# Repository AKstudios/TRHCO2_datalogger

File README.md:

# T/RH/CO2 data logger
A temperature, relative humidity and carbon dioxide data logger that stores time-stamped data in a microSD card at specific logging intervals.

<p align="center">
  
  <br></br>
  
</p>

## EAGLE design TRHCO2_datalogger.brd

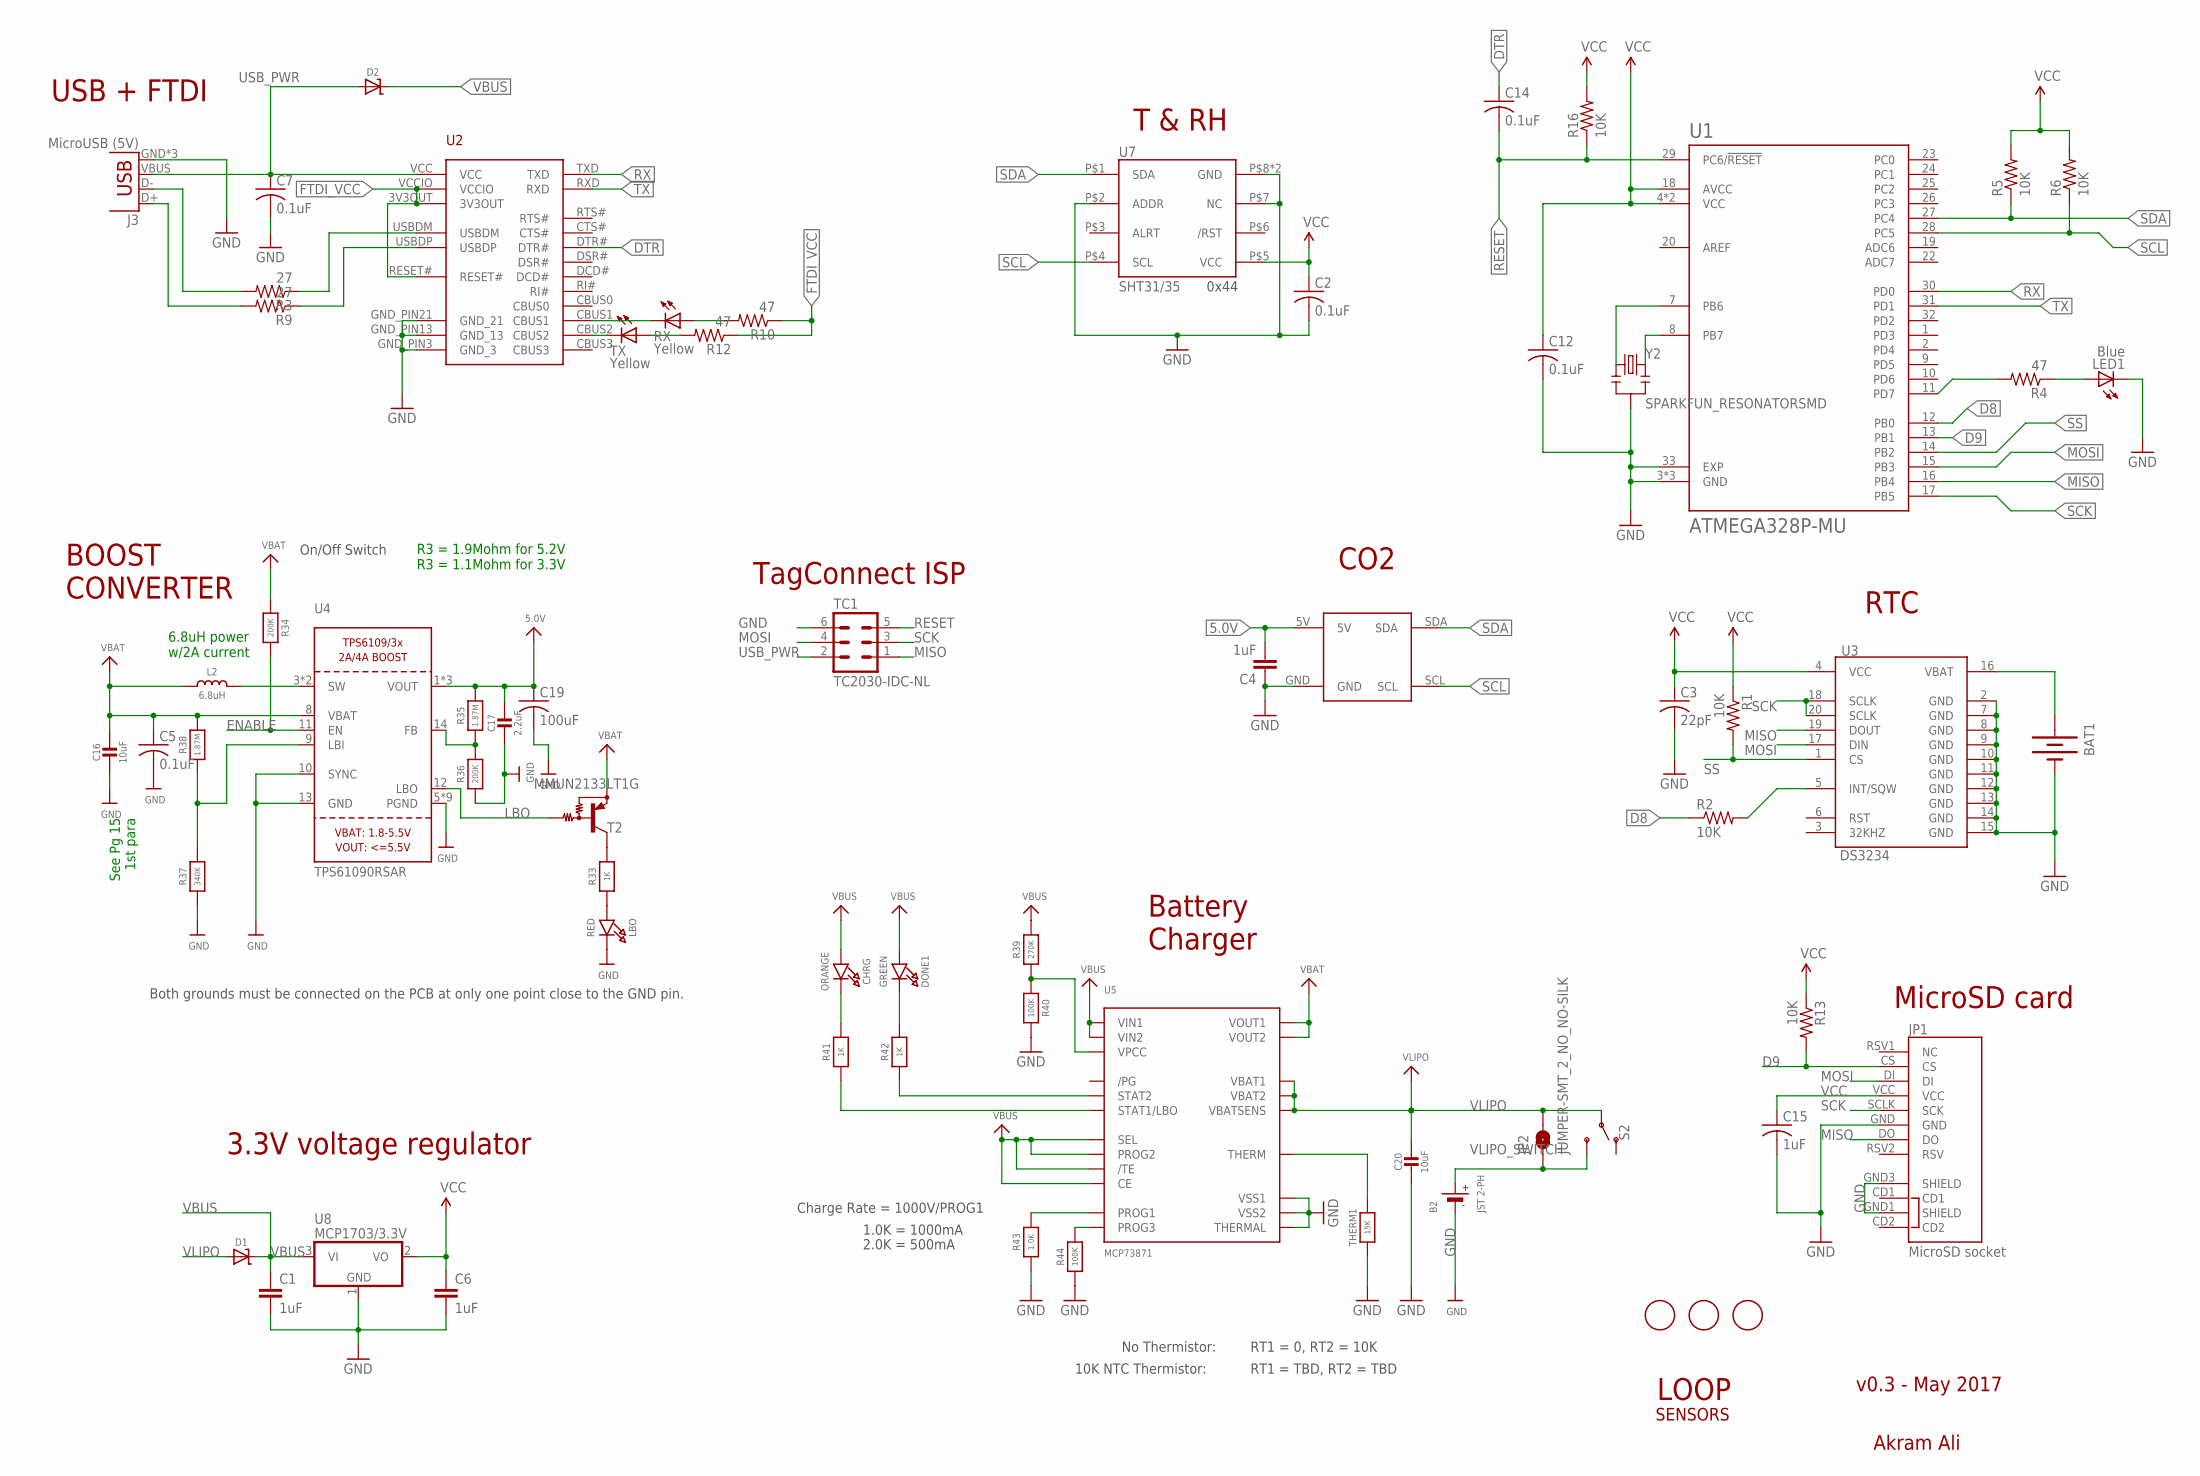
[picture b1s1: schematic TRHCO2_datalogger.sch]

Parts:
B2: JST 2-PH; JSTPH2
BAT1: BATTERY12MM; BATTCON_12MM; MPN 3000
C1, C4, C6: 1uF; 0805; MPN CC0805KKX7R7BB105
C2, C5, C7, C12, C14: 0.1uF; C0402
C3: 22pF; C0402
C15: 1uF; C0402
C16, C20: 10uF; 0805-NO
C17: 2.2uF; 0805-NO
C19: 100uF; C1210
CHRG: ORANGE; CHIPLED_0805_NOOUTLINE
D1, D2: MICROBUILDER_DIODE-SCHOTTKYSOD-123; MICROBUILDER_SOD-123
DONE1: GREEN; CHIPLED_0805_NOOUTLINE
J3: MicroUSB (5V); USB-MICROB; MPN CONN-09505
JP1: MicroSD socket; MICRO-SD-SOCKET-PP
JP2: JUMPER-SMT_2_NO_NO-SILK; SMT-JUMPER_2_NO_NO-SILK
L2: 6.8uH; INDUCTOR_5X5MM_TDK_VLC5045
LBO: RED; CHIPLED_0805_NOOUTLINE
LED1: Blue; CHIPLED_0805; MPN 150080BS75000
R1, R2, R5, R6, R13, R16: 10K; R0402
R3, R9: 27; R0402
R4, R10, R12: 47; R0402
R33, R41, R42: 1K; 0805-NO
R34, R36: 200K; 0805-NO
R35: 1.87M; 0805-NO
R37: 340K; _0805MP
R38: 1.87M; _0805MP
R39: 270K; 0805-NO
R40, R44: 100K; 0805-NO
R43: 1.0K; 0805-NO
RX: Yellow; CHIPLED_0805; MPN LG R971-KN-1
S2: SWITCH-SPDT-SMD-RIGHT-ANGLE; SWITCH_SPST_SMD_A
T2: MMUN2133LT1G; SC59-BEC
TC1: TC2030-IDC-NL
THERM1: 15K; 0805-NO
TX: Yellow; CHIPLED_0805; MPN LH R974-LP-1
U1: ATMEGA328P-MU; QFN50P500X500X100-33N
U2: FT231XQ-R; FTDI_FT231XQ-R_PACKAGE; MPN FT231XQ-R
U3: DS3234; MPN DS3234S#
U4: TPS61090RSAR; PVQFN-16
U5: MCP73871; QFN20_4MM
U6: K30-CO2-I2C
U7: SHT31/35; SHT3X; MPN SHT31-DIS-B
U8: MCP1703/3.3V; SOT23; MPN MCP1703T-2502E/CB
U$1, U$2, U$3: FIDUCIAL; FIDUCIAL_1MM
Y2: SPARKFUN_RESONATORSMD; SPARKFUN_RESONATOR-SMD

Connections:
5.0V: C4.2, C17.1, C19.1, R35.2, U4.1 (VOUT), U4.15 (VOUT), U4.16 (VOUT), U6.5V
D8: R2.1, U1.12 (PB0)
D9: JP1.CS, R13.2, U1.13 (PB1)
DTR: C14.1, U2.DTR#
ENABLE: R34.2, U4.11 (EN)
FTDI_VCC: R10.1, R12.1, U2.3V3OUT, U2.RESET#, U2.VCCIO
GND: B2.1 (-), BAT1.GND (-), C1.2, C2.2, C3.2, C4.1, C5.2, C6.2, C7.2, C12.2, C15.2, C16.2, C17.2, C19.2, C20.2, J3.GND, J3.MT1 (GND), J3.MT2 (GND), JP1.GND, JP1.GND1 (SHIELD), JP1.GND3 (SHIELD), LBO.C, LED1.C, R36.1, R37.1, R40.2, R43.1, R44.1, TC1.6, THERM1.1, U1.3 (GND), U1.5 (GND), U1.21 (GND), U1.33 (EXP), U2.GND_PIN3 (GND_3), U2.GND_PIN13 (GND_13), U2.GND_PIN21 (GND_21), U3.2 (GND), U3.7 (GND), U3.8 (GND), U3.9 (GND), U3.10 (GND), U3.11 (GND), U3.12 (GND), U3.13 (GND), U3.14 (GND), U3.15 (GND), U4.5 (PGND), U4.6 (PGND), U4.7 (PGND), U4.10 (SYNC), U4.13 (GND), U4.P$18 (PGND), U4.P$19 (PGND), U4.P$20 (PGND), U4.P$21 (PGND), U4.P$22 (PGND), U4.THERMAL (PGND), U5.P$10 (VSS1), U5.P$11 (VSS2), U5.P$21 (THERMAL), U6.GND, U7.P$2 (ADDR), U7.P$7 (NC), U7.P$8 (GND), U7.PAD (GND), U8.1 (GND), Y2.2
LBO: T2.B, U4.12 (LBO)
MISO: JP1.DO, TC1.1, U1.16 (PB4), U3.19 (DOUT)
MOSI: JP1.DI, TC1.4, U1.15 (PB3), U3.17 (DIN)
unnamed: R4.2, U1.11 (PD7)
unnamed: R2.2, U3.5 (INT/SQW)
unnamed: LED1.A, R4.1
unnamed: U1.8 (PB7), Y2.3
unnamed: U1.7 (PB6), Y2.1
unnamed: L2.P$2 (2), U4.3 (SW), U4.4 (SW)
unnamed: R37.2, R38.1, U4.9 (LBI)
unnamed: BAT1.PWR@1 (+), U3.16 (VBAT)
unnamed: LBO.A, R33.1
unnamed: RX.C, U2.CBUS1
unnamed: TX.C, U2.CBUS2
unnamed: R3.1, U2.USBDM
unnamed: R9.1, U2.USBDP
unnamed: R10.2, RX.A
unnamed: R35.1, R36.2, U4.14 (FB)
unnamed: R12.2, TX.A
unnamed: R33.2, T2.C
unnamed: R39.1, R40.1, U5.P$2 (VPCC)
unnamed: J3.D-, R3.2
unnamed: J3.D+, R9.2
unnamed: R42.1, U5.P$7 (STAT2)
unnamed: R41.1, U5.P$8 (STAT1/LBO)
unnamed: R43.2, U5.P$13 (PROG1)
unnamed: THERM1.2, U5.P$5 (THERM)
unnamed: DONE1.C, R42.2
unnamed: CHRG.C, R41.2
unnamed: R44.2, U5.P$12 (PROG3)
RESET: C14.2, R16.1, TC1.5, U1.29 (PC6/!RESET)
RX: U1.30 (PD0), U2.TXD
SCK: JP1.SCLK (SCK), TC1.3, U1.17 (PB5), U3.18 (SCLK), U3.20 (SCLK)
SCL: R6.1, U1.28 (PC5), U6.SCL, U7.P$4 (SCL)
SDA: R5.1, U1.27 (PC4), U6.SDA, U7.P$1 (SDA)
SS: R1.2, U1.14 (PB2), U3.1 (CS)
TX: U1.31 (PD1), U2.RXD
USB_PWR: C7.1, D2.A, J3.VBUS, TC1.2, U2.VCC
VBAT: C5.1, C16.1, L2.P$1 (1), R34.1, R38.2, T2.E, U4.8 (VBAT), U5.P$1 (VOUT1), U5.P$20 (VOUT2)
VBUS: C1.1, CHRG.A, D1.C, D2.C, DONE1.A, R39.2, U5.P$3 (SEL), U5.P$4 (PROG2), U5.P$9 (/TE), U5.P$17 (CE), U5.P$18 (VIN1), U5.P$19 (VIN2), U8.3 (VI)
VCC: C2.1, C3.1, C6.1, C12.1, C15.1, JP1.VCC, R1.1, R5.2, R6.2, R13.1, R16.2, U1.4 (VCC), U1.6 (VCC), U1.18 (AVCC), U3.4 (VCC), U7.P$5 (VCC), U8.2 (VO)
VLIPO: C20.1, D1.A, JP2.2, S2.2, U5.P$14 (VBAT1), U5.P$15 (VBAT2), U5.P$16 (VBATSENS)
VLIPO_SWITCH: B2.2 (+), JP2.1, S2.3 (S)

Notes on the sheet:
T & RH
3.3V voltage regulator
LOOP
Akram Ali
USB + FTDI
0x44
CO2
MicroSD card
RTC
v0.3 - May 2017
SENSORS
Both grounds must be connected on the PCB at only one point close to the GND pin.
On/Off Switch
See Pg 15 1st para
6.8uH power w/2A current
R3 = 1.9Mohm for 5.2V R3 = 1.1Mohm for 3.3V
Charge Rate = 1000V/PROG1
1.0K = 1000mA
2.0K = 500mA
No Thermistor:
10K NTC Thermistor:
RT1 = 0, RT2 = 10K
RT1 = TBD, RT2 = TBD
BOOST CONVERTER
Battery Charger
TagConnect ISP

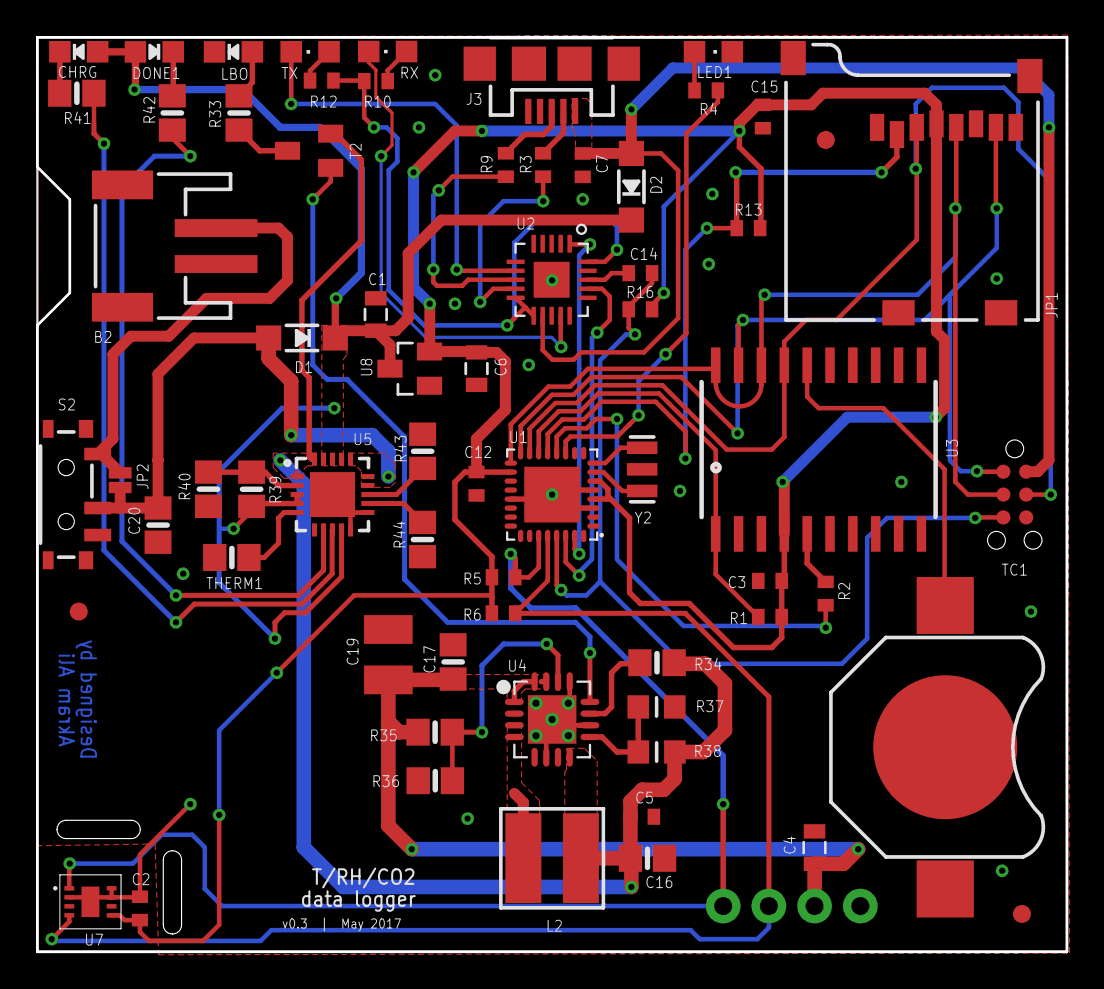
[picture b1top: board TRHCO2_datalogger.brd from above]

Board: 2 copper layers, 57.2 x 50.8 mm, 67 parts (0 on the bottom side), 50 nets.

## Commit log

2017-01-13 Added EAGLE files
2017-01-17 Completed v0.1 design
    Routed all traces
2017-01-18 Added D battery input headers
    Requires boost converter (https://www.sparkfun.com/products/10255) to allow 2 D batteries to supply at least 3V and get output 5V, 500mA
2017-01-19 Traces adjusted
    Cleared some spacing between traces and vias
    Added MPN for some components
2017-01-19 Minor fixes
2017-01-28 Added OSH Park renders
2017-02-08 v0.2 - Major fixes
    - Flipped header for LiPo boost. + and - are now facing up
    - Added pullup on DS3234 clock - so there is no interference while
    flashing bootloader (can be removed by desoldering jumper)
    - Added NPN transistor in the circuit to switch microSD card on/off for
    previous adaptations of Sdfat library
    - Routed CS pin of microSD card to ISP header for debug when necessary
2017-02-08 Updated OSH park renders
2017-02-08 Deleted v0.1 renders
2017-02-08 Added v0.2 OSH park renders
2017-02-15 v0.1 firmware added
    Use latest Arduino IDE (1.8.1) and latest Sdfat library
2017-05-21 v0.3 - major update
    - Added boost converter (TPS61090)
    - Added switch for battery
    - Replaced ISP header with TagConnect pins
    - Added pullups on all SPI devices
    - Removed transistor from sensors and SD card
    - Removed jumper @ DS3234 pull up
2017-05-22 Added power plane
    Adjusted traces, added power planes, some other minor trace adjustments
2017-06-15 Firmware update - set interval from microSD card
    Logging interval can be written in a file called config.txt. Must be a
    number between 1-86,400 seconds. Defaults to 30 seconds if incorrect
    format used or if file not found.
2017-06-15 Add units to serial print
2018-08-13 Revert "update"
    This reverts commit 3fd739265b7c9a937414b5746fef9af12a5aee94.
2018-08-13 Revert "Initial commit"
    This reverts commit c60d50e7691b51f36b2304322911fcaf5220ad07.
2018-08-13 Revert "Add units to serial print"
    This reverts commit 42bc8d94add604d970789fbf07ac64797589f6a5.

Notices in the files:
parts and their libraries:
SparkFun-Connectors: Licensing: Creative Commons ShareAlike 4.0 International - https://creativecommons.org/licenses/by-sa/4.0
microbuilder: This work is placed in the public domain, and may be freely used for commercial and non-commercial work with the following conditions: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
